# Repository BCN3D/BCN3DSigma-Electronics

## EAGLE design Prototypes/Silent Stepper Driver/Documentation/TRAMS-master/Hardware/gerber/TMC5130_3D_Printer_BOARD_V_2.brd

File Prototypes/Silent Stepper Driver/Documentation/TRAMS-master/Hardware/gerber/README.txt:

TRAMS v0.91

4 Layer PCB
35 um Copper
1.6mm thickness

Do not buy and assemble D2, D4, D6. 
Only D5 is needed.

Do not assemble all THT parts but ship them with the PCBs.

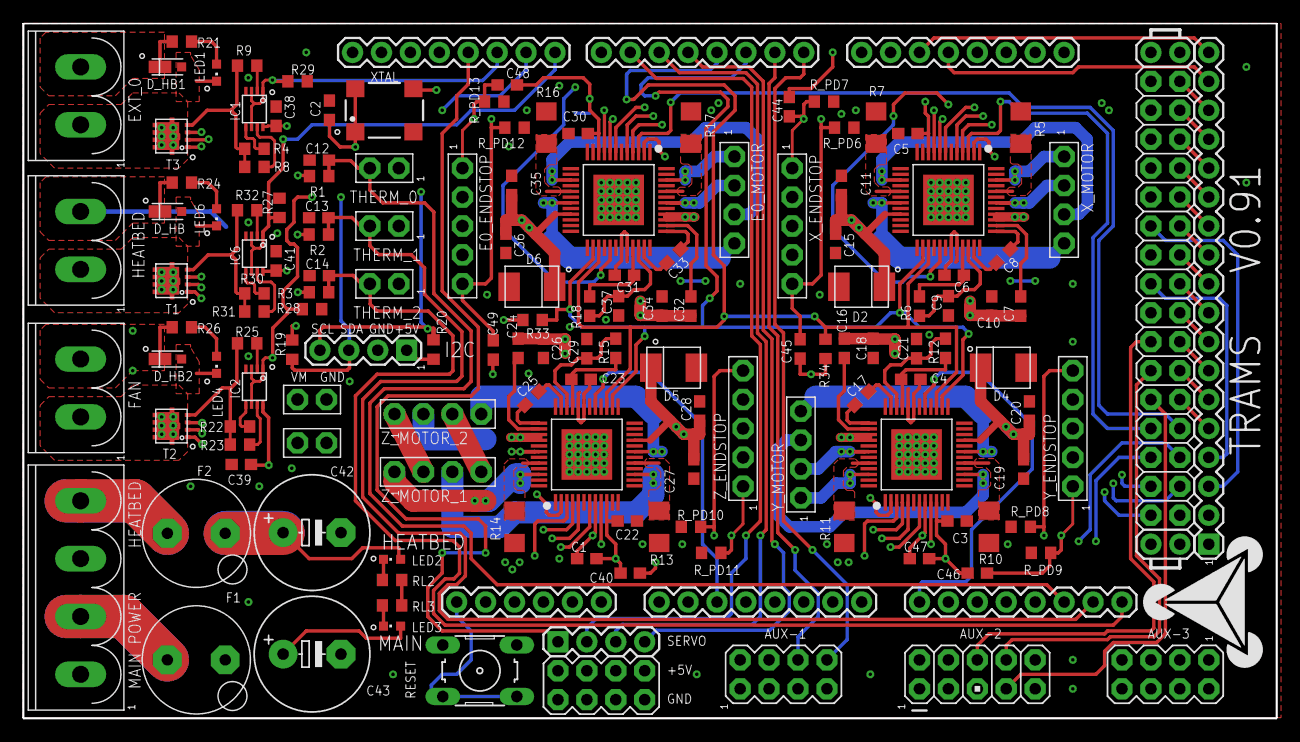
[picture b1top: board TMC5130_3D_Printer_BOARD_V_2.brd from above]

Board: 4 copper layers, 110.0 x 61.0 mm, 147 parts (1 on the bottom side), 137 nets.

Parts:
AUX-1, AUX-3: 2X4
AUX-2: AVR_ICSP
AUX-4: 1X18
C1, C40, C44, C45, C46, C47, C48, C49: 1nF; 0603
C2, C3, C5, C7, C10, C12, C13, C14, C15, C16, C18, C20, C22, C24, C26, C28, C30, C32, C34, C36, C38, C39, C41: 100nF; C0603
C4, C6, C11, C19, C23, C27, C31, C35: 4.7µF; C0603
C8, C17, C25, C33: 22nF; C0603
C9, C21, C37: 470nF; 0603
C29: C0603/470nF/16V; C0603
C42, C43: 1000µ 30V; E5-10,5
D2, D4, D5, D6: SMBJ43A; SMB
D_HB, D_HB1, D_HB2: MSS1P6; MICRO_SMP
E0_ENDSTOP: 5PIN_1ROWTHT; 5PIN_1ROW_2.54_THT
E0_MOTOR: 4PIN_1ROW_2.54_THT
EX_0: RIA_AKL_220_2_PINS
F1, F2: LITTLEFUSE_TR5_383_SERIES
FAN: RIA_AKL_220_2_PINS
HEATBED: RIA_AKL_220_2_PINS
I2C: 1X04
IC1, IC2, IC6: SN74LVC3G17DCUR; US8_DCU
LED1, LED4, LED6: RED; CHIPLED_0603
LED2, LED3: GREEN; CHIPLED_0603
MAIN_IN: RIA_AKL_220_4_PINS
R1, R2, R3, R19, R20, R21, R24, R26, R27, R28, R29, R33, R34: 4.7kΩ; R0603
R4, R8, R9, R22, R23, R25, R30, R31, R32: 100Ω; R0603
R5, R7, R10, R11, R13, R14, R16, R17: R1206,0R15/0.5W; R1206
R6, R12, R15, R18: 2.2Ω; 0603
RL2, RL3: 4.7kΩ; R0603
R_PD6, R_PD7, R_PD8, R_PD9, R_PD10, R_PD11, R_PD12, R_PD13: 100kΩ; R0603
S1: B3F-10XX
SERVO: 1X04
SERV_SUPPLY: 2X4
SHIELD: ARDUINO_MEGA_SHIELD_BIG; ARDUINO_MEGA_SHIELD
T1, T2, T3: AON7508; DFN3X3_8L
THERM0, THERM1, THERM2: 2PIN_1ROW; 2PIN_1ROW_2.54_THT
TMC1, TMC2, TMC3, TMC5130: QFP50P900X900X113-49N_NOFID
U$10: TRINAMIC_LOGO_WHITE_NOTEXT
U$11: TRAMS_PRINT
VM0, VM1: 2PIN_1ROW; 2PIN_1ROW_2.54_THT
XTAL: SM77H 16MHz; SM77H
X_ENDSTOP: 5PIN_1ROWTHT; 5PIN_1ROW_2.54_THT
X_MOTOR: 4PIN_1ROW_2.54_THT
Y_ENDSTOP: 5PIN_1ROWTHT; 5PIN_1ROW_2.54_THT
Y_MOTOR: 4PIN_1ROW_2.54_THT
Z_ENDSTOP: 5PIN_1ROWTHT; 5PIN_1ROW_2.54_THT
Z_MOTOR_1, Z_MOTOR_2: 4PIN_1ROW_2.54_THT

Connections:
+5V: AUX-1.1, AUX-1.2, AUX-2.1, AUX-3.1, AUX-4.1, C1.2, C2.2, C3.1, C5.1, C22.1, C30.1, C38.1, C39.1, C40.2, C41.1, C44.2, C45.2, C46.2, C47.2, C48.2, C49.2, E0_ENDSTOP.2, E0_ENDSTOP.4, I2C.1, IC1.8, IC2.8, IC6.8, R1.2, R2.2, R3.2, R19.2, R20.2, R33.1, R34.1, SERV_SUPPLY.1, SERV_SUPPLY.3, SERV_SUPPLY.5, SERV_SUPPLY.7, SHIELD.5V@0, SHIELD.5V@1, SHIELD.5V@2, TMC1.10, TMC2.10, TMC3.10, TMC5130.10, XTAL.1, XTAL.4, X_ENDSTOP.2, X_ENDSTOP.4, Y_ENDSTOP.2, Y_ENDSTOP.4, Z_ENDSTOP.2, Z_ENDSTOP.4
A3: AUX-1.5, SHIELD.A3
A4: AUX-1.7, SHIELD.A4
A5: AUX-2.3, SHIELD.A5
A9: AUX-2.4, SHIELD.A9
A10: AUX-2.5, SHIELD.A10
A11: AUX-2.10, SHIELD.A11
A12: AUX-2.9, SHIELD.A12
CLK: TMC1.2, TMC2.2, TMC3.2, TMC5130.2, XTAL.3
CS_E0: SHIELD.47, TMC3.3
CS_X: SHIELD.46, TMC5130.3
CS_Y: SHIELD.49, TMC1.3
CS_Z: SHIELD.48, TMC2.3
D0: AUX-1.8, SHIELD.0
D1: AUX-1.6, SHIELD.1
D4: SERVO.4, SHIELD.4
D5: SERVO.3, SHIELD.5
D6: SERVO.2, SHIELD.6
D11: SERVO.1, SHIELD.11
D16: AUX-4.18, SHIELD.16
D17: AUX-4.17, SHIELD.17
D23: AUX-4.16, SHIELD.23
D25: AUX-4.15, SHIELD.25
D27: AUX-4.14, SHIELD.27
D29: AUX-4.13, SHIELD.29
D31: AUX-4.12, SHIELD.31
D32: AUX-4.3, SHIELD.32
D33: AUX-4.11, SHIELD.33
D34: AUX-3.2, SHIELD.34
D35: AUX-4.10, SHIELD.35
D36: AUX-4.4, SHIELD.36
D37: AUX-4.9, SHIELD.37
D39: AUX-4.8, SHIELD.39
D40: AUX-2.6, SHIELD.40
D41: AUX-4.7, SHIELD.41
D42: AUX-2.8, SHIELD.42
D43: AUX-4.6, SHIELD.43
D44: AUX-2.7, SHIELD.44
D45: AUX-4.5, SHIELD.45
D53: AUX-3.6, SHIELD.53
DRV_EN_E0: SHIELD.24, TMC3.29
DRV_EN_X: SHIELD.38, TMC5130.29
DRV_EN_Y: SHIELD.A8, TMC1.29
DRV_EN_Z: SHIELD.A2, TMC2.29
ENDSTOP_E0_LEFT: C49.1, E0_ENDSTOP.5, R_PD12.2, TMC3.8
ENDSTOP_E0_RIGHT: C48.1, E0_ENDSTOP.1, R_PD13.2, TMC3.9
ENDSTOP_X_LEFT: C45.1, R_PD6.2, TMC5130.8, X_ENDSTOP.5
ENDSTOP_X_RIGHT: C44.1, R_PD7.2, TMC5130.9, X_ENDSTOP.1
ENDSTOP_Y_LEFT: C47.1, R_PD8.2, TMC1.8, Y_ENDSTOP.5
ENDSTOP_Y_RIGHT: C46.1, R_PD9.2, TMC1.9, Y_ENDSTOP.1
ENDSTOP_Z_LEFT: C1.1, R_PD10.2, TMC2.8, Z_ENDSTOP.5
ENDSTOP_Z_RIGHT: C40.1, R_PD11.2, TMC2.9, Z_ENDSTOP.1
FAN: IC2.1, IC2.3, IC2.6, R28.1, SHIELD.9
GND: AUX-1.3, AUX-1.4, AUX-2.2, AUX-3.7, AUX-4.2, C2.1, C3.2, C4.2, C5.2, C6.2, C9.1, C10.1, C11.2, C12.1, C13.1, C14.1, C15.1, C18.1, C19.2, C20.1, C21.1, C22.2, C23.2, C26.1, C27.2, C28.1, C29.1, C30.2, C31.2, C34.1, C35.2, C36.1, C37.1, C38.2, C39.2, C41.2, C42.-, C43.-, D2.A, D4.A, D5.A, D6.A, E0_ENDSTOP.3, I2C.2, IC1.4, IC2.4, IC6.4, MAIN_IN.P$1, MAIN_IN.P$3, R5.1, R7.1, R10.1, R11.1, R13.1, R14.1, R16.1, R17.1, R27.2, R28.2, R29.2, RL2.1, RL3.1, R_PD6.1, R_PD7.1, R_PD8.1, R_PD9.1, R_PD10.1, R_PD11.1, R_PD12.1, R_PD13.1, S1.1, S1.2, SERV_SUPPLY.2, SERV_SUPPLY.4, SERV_SUPPLY.6, SERV_SUPPLY.8, SHIELD.GND@0, SHIELD.GND@1, SHIELD.GND@2, SHIELD.GND@3, SHIELD.GND@4, T1.S0, T1.S1, T1.S2, T2.S0, T2.S1, T2.S2, T3.S0, T3.S1, T3.S2, THERM0.1, THERM1.1, THERM2.1, TMC1.1, TMC1.6, TMC1.11, TMC1.13, TMC1.23, TMC1.31, TMC1.32, TMC1.36, TMC1.48, TMC1.PAD, TMC2.1, TMC2.6, TMC2.11, TMC2.13, TMC2.23, TMC2.31, TMC2.32, TMC2.36, TMC2.48, TMC2.PAD, TMC3.1, TMC3.6, TMC3.11, TMC3.13, TMC3.23, TMC3.31, TMC3.32, TMC3.36, TMC3.48, TMC3.PAD, TMC5130.1, TMC5130.6, TMC5130.11, TMC5130.13, TMC5130.23, TMC5130.31, TMC5130.32, TMC5130.36, TMC5130.48, TMC5130.PAD, VM0.1, VM1.1, XTAL.2, X_ENDSTOP.3, Y_ENDSTOP.3, Z_ENDSTOP.3
HEATBED: IC6.1, IC6.3, IC6.6, R27.1, SHIELD.8
HEATBED_POWER: F2.P$1, MAIN_IN.P$4
HEAT_E0: IC1.1, IC1.3, IC1.6, R29.1, SHIELD.10
INTERRUPT: R33.2, SHIELD.2, TMC1.26, TMC2.26, TMC3.26, TMC5130.26
M1A1_E0: E0_MOTOR.1, TMC3.46
M1A1_X: TMC5130.46, X_MOTOR.1
M1A1_Y: TMC1.46, Y_MOTOR.1
M1A1_Z: TMC2.46, Z_MOTOR_1.1
M1A2_E0: E0_MOTOR.2, TMC3.42
M1A2_X: TMC5130.42, X_MOTOR.2
M1A2_Y: TMC1.42, Y_MOTOR.2
M1A2_Z: TMC2.42, Z_MOTOR_2.2
M1B1_E0: E0_MOTOR.3, TMC3.15
M1B1_X: TMC5130.15, X_MOTOR.3
M1B1_Y: TMC1.15, Y_MOTOR.3
M1B1_Z: TMC2.15, Z_MOTOR_1.3
M1B2_E0: E0_MOTOR.4, TMC3.19
M1B2_X: TMC5130.19, X_MOTOR.4
M1B2_Y: TMC1.19, Y_MOTOR.4
M1B2_Z: TMC2.19, Z_MOTOR_2.4
MAIN_POWER: F1.P$1, MAIN_IN.P$2
MISO: AUX-3.3, SHIELD.50, TMC1.7, TMC2.7, TMC3.7, TMC5130.7
MOSI: AUX-3.4, SHIELD.51, TMC1.5, TMC2.5, TMC3.5, TMC5130.5
unnamed: Z_MOTOR_1.2, Z_MOTOR_2.1
unnamed: Z_MOTOR_1.4, Z_MOTOR_2.3
unnamed: C17.1, TMC1.37
unnamed: C17.2, TMC1.35
unnamed: C16.2, TMC1.38
unnamed: C6.1, R6.1, TMC5130.33
unnamed: C8.1, TMC5130.37
unnamed: C8.2, TMC5130.35
unnamed: C7.2, TMC5130.38
unnamed: C9.2, R6.2, TMC5130.34
unnamed: C21.2, R12.2, TMC1.34
unnamed: C4.1, R12.1, TMC1.33
unnamed: C25.1, TMC2.37
unnamed: C25.2, TMC2.35
unnamed: C24.2, TMC2.38
unnamed: C29.2, R15.2, TMC2.34
unnamed: C23.1, R15.1, TMC2.33
unnamed: C33.1, TMC3.37
unnamed: C33.2, TMC3.35
unnamed: C32.2, TMC3.38
unnamed: C37.2, R18.2, TMC3.34
unnamed: C31.1, R18.1, TMC3.33
unnamed: LED3.C, RL3.2
unnamed: LED2.C, RL2.2
unnamed: LED6.A, R24.1
unnamed: D_HB1.A, EX_0.P$1, LED1.C, T3.D0, T3.D1, T3.D2, T3.D3, T3.D4, T3.D5, T3.D6
unnamed: R4.1, R8.1, R9.1, T3.G
unnamed: IC1.7, R8.2
unnamed: IC1.5, R4.2
unnamed: IC1.2, R9.2
unnamed: LED1.A, R21.1
unnamed: D_HB2.A, FAN.P$1, LED4.C, T2.D0, T2.D1, T2.D2, T2.D3, T2.D4, T2.D5, T2.D6
unnamed: R22.1, R23.1, R25.1, T2.G
unnamed: D_HB.A, HEATBED.P$1, LED6.C, T1.D0, T1.D1, T1.D2, T1.D3, T1.D4, T1.D5, T1.D6
unnamed: R30.1, R31.1, R32.1, T1.G
unnamed: IC2.7, R23.2
unnamed: IC2.5, R22.2
unnamed: IC6.7, R31.2
unnamed: IC6.5, R30.2
unnamed: IC6.2, R32.2
unnamed: IC2.2, R25.2
unnamed: LED4.A, R26.1
POSPULSE: R34.2, SHIELD.3, TMC1.27, TMC2.27, TMC3.27, TMC5130.27
RESET: S1.3, S1.4, SHIELD.RESET
SCK: AUX-3.5, SHIELD.52, TMC1.4, TMC2.4, TMC3.4, TMC5130.4
SCL: I2C.4, R20.1, SHIELD.21
SDA: I2C.3, R19.1, SHIELD.20
SENSE1: R5.2, TMC5130.44
SENSE2: R7.2, TMC5130.17
SENSE3: R10.2, TMC1.17
SENSE4: R11.2, TMC1.44
SENSE5: R13.2, TMC2.17
SENSE6: R14.2, TMC2.44
SENSE7: R16.2, TMC3.17
SENSE8: R17.2, TMC3.44
THERM0: C12.2, R1.1, SHIELD.A13, THERM0.2
THERM1: C13.2, R2.1, SHIELD.A14, THERM1.2
THERM2: C14.2, R3.1, SHIELD.A15, THERM2.2
VM: C7.1, C10.2, C11.1, C15.2, C16.1, C18.2, C19.1, C20.2, C24.1, C26.2, C27.1, C28.2, C32.1, C34.2, C35.1, C36.2, C43.+, D2.C, D4.C, D5.C, D6.C, D_HB1.C, D_HB2.C, EX_0.P$2, F1.P$2, FAN.P$2, LED3.A, R21.2, R26.2, TMC1.21, TMC1.39, TMC1.40, TMC2.21, TMC2.39, TMC2.40, TMC3.21, TMC3.39, TMC3.40, TMC5130.21, TMC5130.39, TMC5130.40, VM0.2, VM1.2
V_HEATBED: C42.+, D_HB.C, F2.P$2, HEATBED.P$2, LED2.A, R24.2

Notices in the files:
parts and their libraries:
SparkFun-Connectors: Licensing: Creative Commons ShareAlike 4.0 International - https://creativecommons.org/licenses/by-sa/4.0
